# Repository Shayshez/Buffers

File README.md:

# Buffers
6 Individual Buffers / Buffered multiple
based on links by Émilie Gillet
CC-BY-SA 3.0

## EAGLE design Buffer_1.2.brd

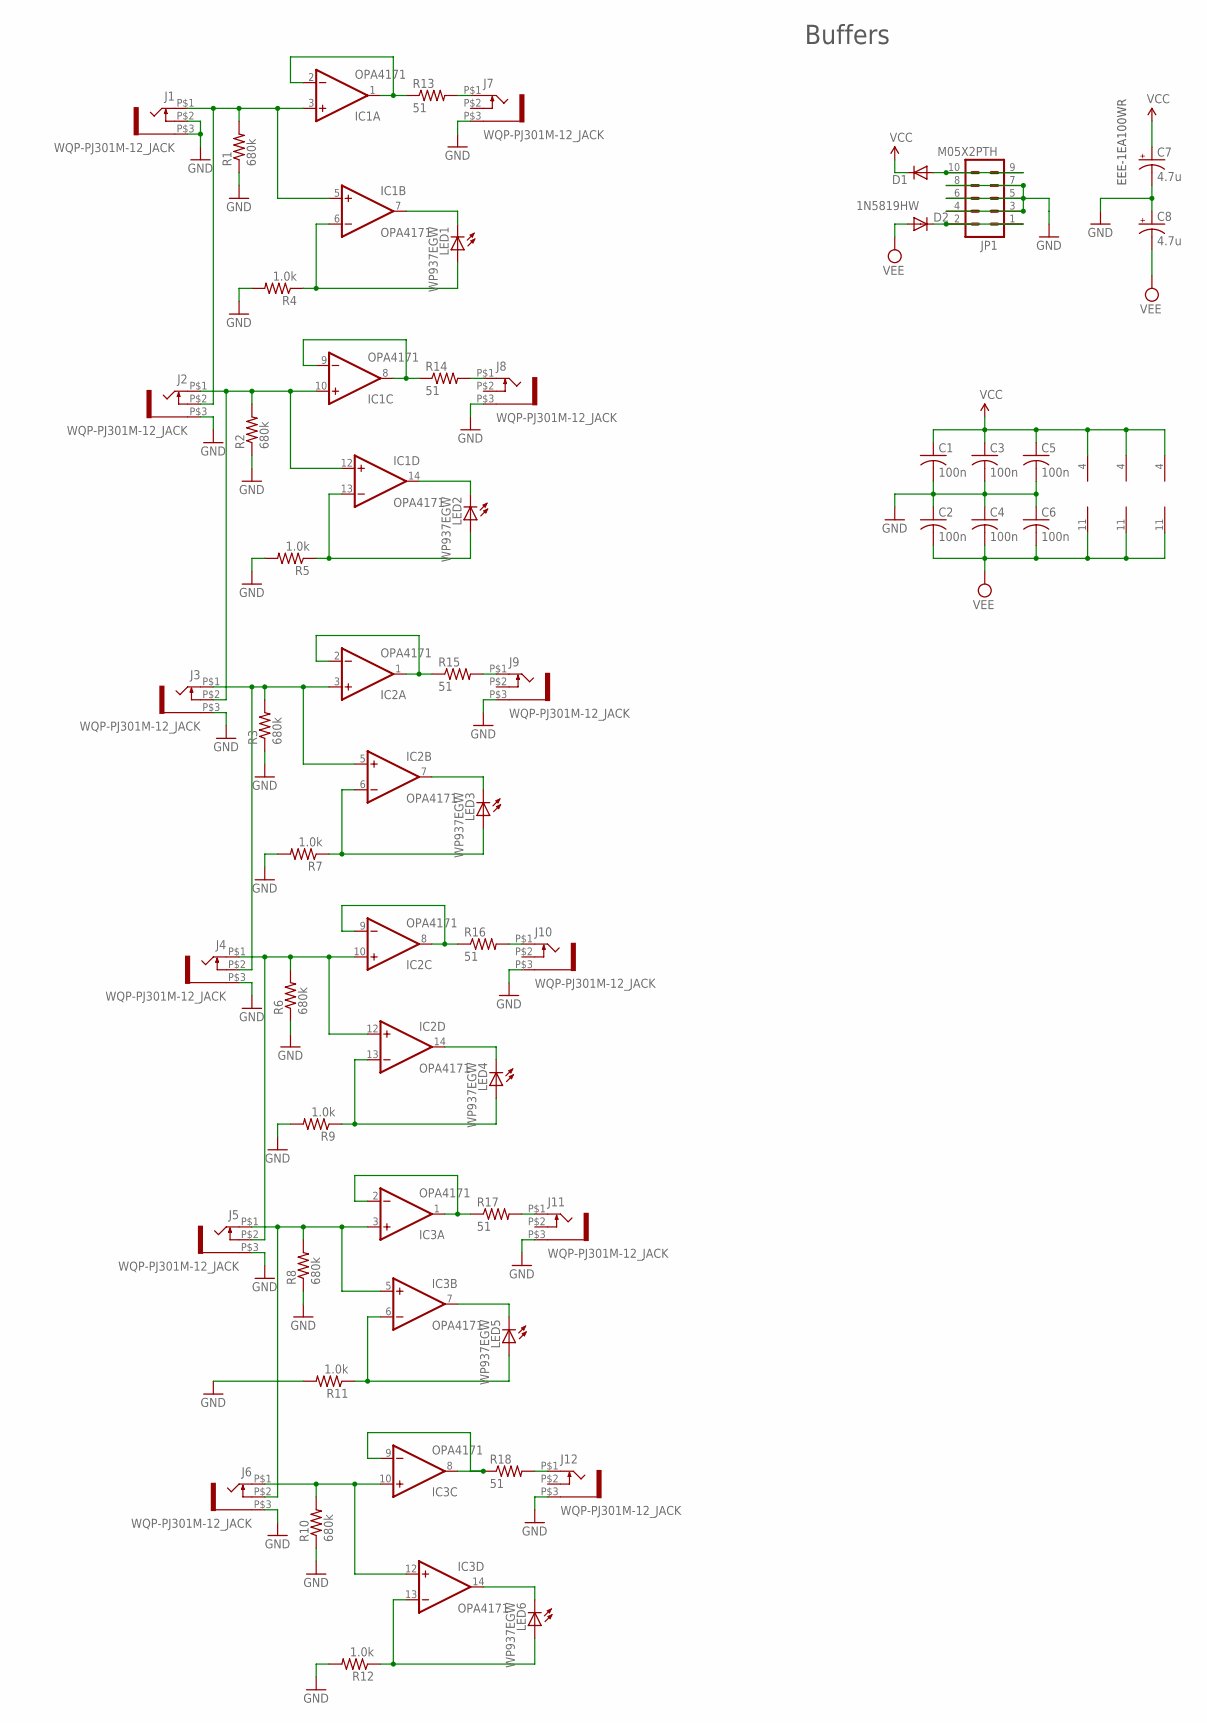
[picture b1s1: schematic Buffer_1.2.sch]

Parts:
C1, C2, C3, C4, C5, C6: 100n; C0603
C7, C8: 4.7u; PANASONIC_A
D1, D2: 1N5819HW; SOD123
IC1, IC2, IC3: OPA4171; TSSOP14
J1, J2, J3, J4, J5, J6, J7, J8, J9, J10, J11, J12: WQP-PJ301M-12_JACK
JP1: M05X2PTH; AVR_ICSP
LED1, LED2, LED3, LED4, LED5, LED6: WP937EGW; LED3MM
R1, R2, R3, R6, R8, R10: 680k; R0603
R4, R5, R7, R9, R11, R12: 1.0k; R0603
R13, R14, R15, R16, R17, R18: 51; R0603

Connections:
GND: C1.2, C2.1, C3.2, C4.1, C5.2, C6.1, C7.-, C8.+, J1.P$2 (3), J1.P$3 (1), J2.P$3 (1), J3.P$3 (1), J4.P$3 (1), J5.P$3 (1), J6.P$3 (1), J7.P$3 (1), J8.P$3 (1), J9.P$3 (1), J10.P$3 (1), J11.P$3 (1), J12.P$3 (1), JP1.3, JP1.4, JP1.5, JP1.6, JP1.7, JP1.8, R1.1, R2.1, R3.1, R4.2, R5.2, R6.1, R7.2, R8.1, R9.2, R10.1, R11.2, R12.2
unnamed: IC1.3 (+IN), IC1.5 (+IN), J1.P$1 (2), J2.P$2 (3), R1.2
unnamed: IC1.14 (OUT), LED2.K (C)
unnamed: IC1.1 (OUT), IC1.2 (-IN), R13.1
unnamed: IC1.13 (-IN), LED2.A, R5.1
unnamed: IC2.1 (OUT), IC2.2 (-IN), R15.1
unnamed: D2.C, JP1.1, JP1.2
unnamed: J9.P$1 (2), R15.2
unnamed: IC1.7 (OUT), LED1.K (C)
unnamed: IC2.3 (+IN), IC2.5 (+IN), J3.P$1 (2), J4.P$2 (3), R3.2
unnamed: J7.P$1 (2), R13.2
unnamed: J8.P$1 (2), R14.2
unnamed: IC2.8 (OUT), IC2.9 (-IN), R16.1
unnamed: J10.P$1 (2), R16.2
unnamed: J11.P$1 (2), R17.2
unnamed: IC1.8 (OUT), IC1.9 (-IN), R14.1
unnamed: IC2.10 (+IN), IC2.12 (+IN), J4.P$1 (2), J5.P$2 (3), R6.2
unnamed: IC2.7 (OUT), LED3.K (C)
unnamed: J12.P$1 (2), R18.2
unnamed: IC2.6 (-IN), LED3.A, R7.1
unnamed: D1.A, JP1.9, JP1.10
unnamed: IC1.6 (-IN), LED1.A, R4.1
unnamed: IC1.10 (+IN), IC1.12 (+IN), J2.P$1 (2), J3.P$2 (3), R2.2
unnamed: IC2.14 (OUT), LED4.K (C)
unnamed: IC2.13 (-IN), LED4.A, R9.1
unnamed: IC3.1 (OUT), IC3.2 (-IN), R17.1
unnamed: IC3.3 (+IN), IC3.5 (+IN), J5.P$1 (2), J6.P$2 (3), R8.2
unnamed: IC3.8 (OUT), IC3.9 (-IN), R18.1
unnamed: IC3.10 (+IN), IC3.12 (+IN), J6.P$1 (2), R10.2
unnamed: IC3.7 (OUT), LED5.K (C)
unnamed: IC3.6 (-IN), LED5.A, R11.1
unnamed: IC3.14 (OUT), LED6.K (C)
unnamed: IC3.13 (-IN), LED6.A, R12.1
VCC: C1.1, C3.1, C5.1, C7.+, D1.C, IC1.4 (V+), IC2.4 (V+), IC3.4 (V+)
VEE: C2.2, C4.2, C6.2, C8.-, D2.A, IC1.11 (V-), IC2.11 (V-), IC3.11 (V-)

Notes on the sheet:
Buffers
EEE-1EA100WR

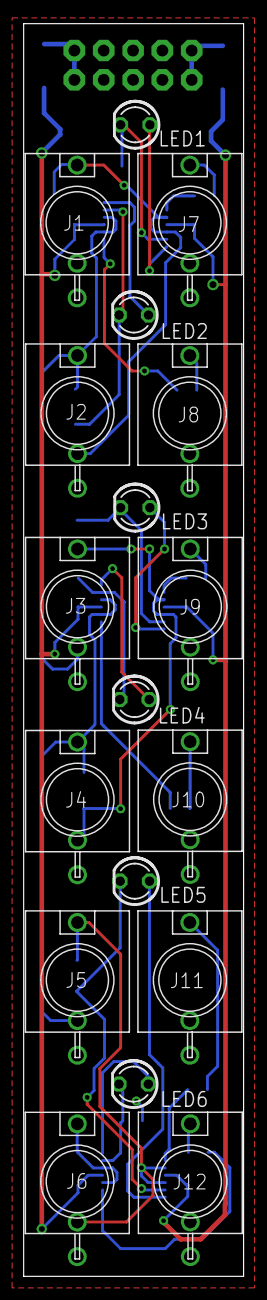
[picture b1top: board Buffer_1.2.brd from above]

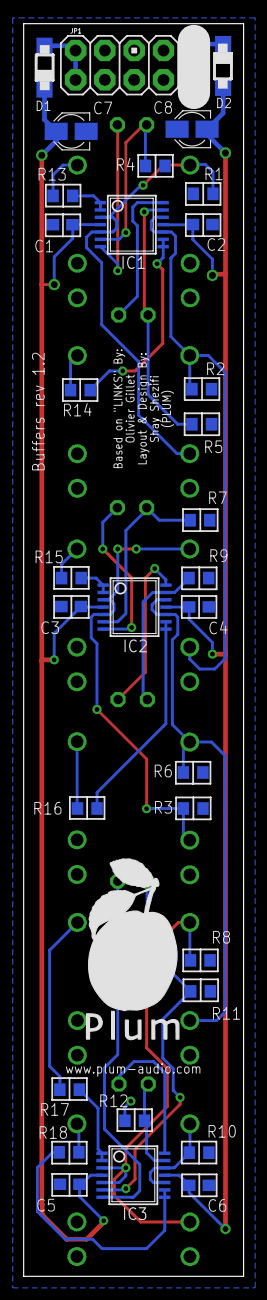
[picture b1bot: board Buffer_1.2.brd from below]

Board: 2 copper layers, 19.1 x 108.5 mm, 50 parts (32 on the bottom side), 35 nets.

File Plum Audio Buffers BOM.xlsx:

Qty | Value | Device | Package | Parts | Description
6.0 | 1.0k | R-US_R0603 | R0603 | R4, R5, R7, R9, R11, R12 | RESISTOR 1.0k
6.0 | 51R | R-US_R0603 | R0603 | R13, R14, R15, R16, R17, R18 | RESISTOR 6R
6.0 | 680k | R-US_R0603 | R0603 | R1, R2, R3, R6, R8, R10 | RESISTOR 680k
6.0 | 100n | C-USC0603 | C0603 | C1, C2, C3, C4, C5, C6 | CAPACITOR 100n
2.0 | 4.7u | CPOL-USA | PANASONIC_A | C7, C8 | POLARIZED CAPACITOR electrolytic 4.7uf
2.0 | 1N5819HW | DIODE-SOD123 | SOD123 | D1, D2 | DIODE
3.0 | OPA4171 | TL074PW | TSSOP14 | IC1, IC2, IC3 | OP AMP / TL072CPWR Can be used (but less accurate)
6.0 | WP937EGW | LED3MM | LED3MM | LED1, LED2, LED3, LED4, LED5, LED6 | LED DUAL COLOR R/G
1.0 | M05X2PTH | M05X2PTH | AVR_ICSP | JP1 | Header 5x2 for power
12.0 | WQP-PJ301M-12_JACK | WQP-PJ301M-12_JACK | WQP-PJ301M-12_JACK | J1, J2, J3, J4, J5, J6, J7, J8, J9, J10, J11, J12 | Thonkiconn
